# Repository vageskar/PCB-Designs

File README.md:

# PCB-Designs
PCB designs using Cadsoft Eagle

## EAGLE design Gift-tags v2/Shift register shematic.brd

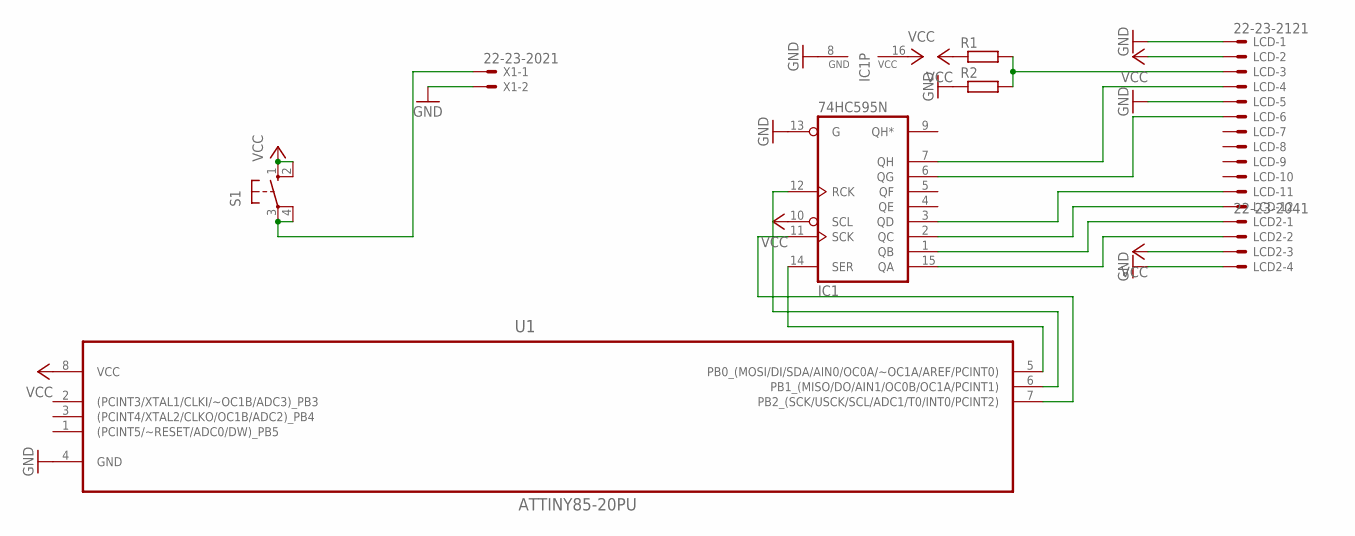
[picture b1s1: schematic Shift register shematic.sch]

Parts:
IC1: 74HC595N; DIL16
LCD: 22-23-2121
LCD2: 22-23-2041
R1, R2: R-EU_0207/10; 0207/10
S1: 40-XX; B3F-40XX
U1: ATTINY85-20PU; DIP254P762X533-8
X1: 22-23-2021

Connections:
GND: IC1.8 (GND), IC1.13 (G), LCD.1, LCD.5, LCD2.4, R2.1, U1.4 (GND), X1.2
unnamed: IC1.15 (QA), LCD2.2
unnamed: IC1.1 (QB), LCD2.1
unnamed: IC1.2 (QC), LCD.12
unnamed: IC1.3 (QD), LCD.11
unnamed: IC1.6 (QG), LCD.6
unnamed: IC1.7 (QH), LCD.4
unnamed: IC1.14 (SER), U1.5 (PB0_(MOSI/DI/SDA/AIN0/OC0A/~OC1A/AREF/P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)
unnamed: IC1.12 (RCK), U1.6 (PB1_(MISO/DO/AIN1/OC0B/OC1A/PCINT1))
unnamed: IC1.11 (SCK), U1.7 (PB2_(SCK/USCK/SCL/ADC1/T0/INT0/PCINT2))
unnamed: LCD.3, R1.2, R2.2
unnamed: S1.3, S1.4 (P1), X1.1
VCC: IC1.10 (SCL), IC1.16 (VCC), LCD.2, LCD2.3, R1.1, S1.1 (S), S1.2 (S1), U1.8 (VCC)

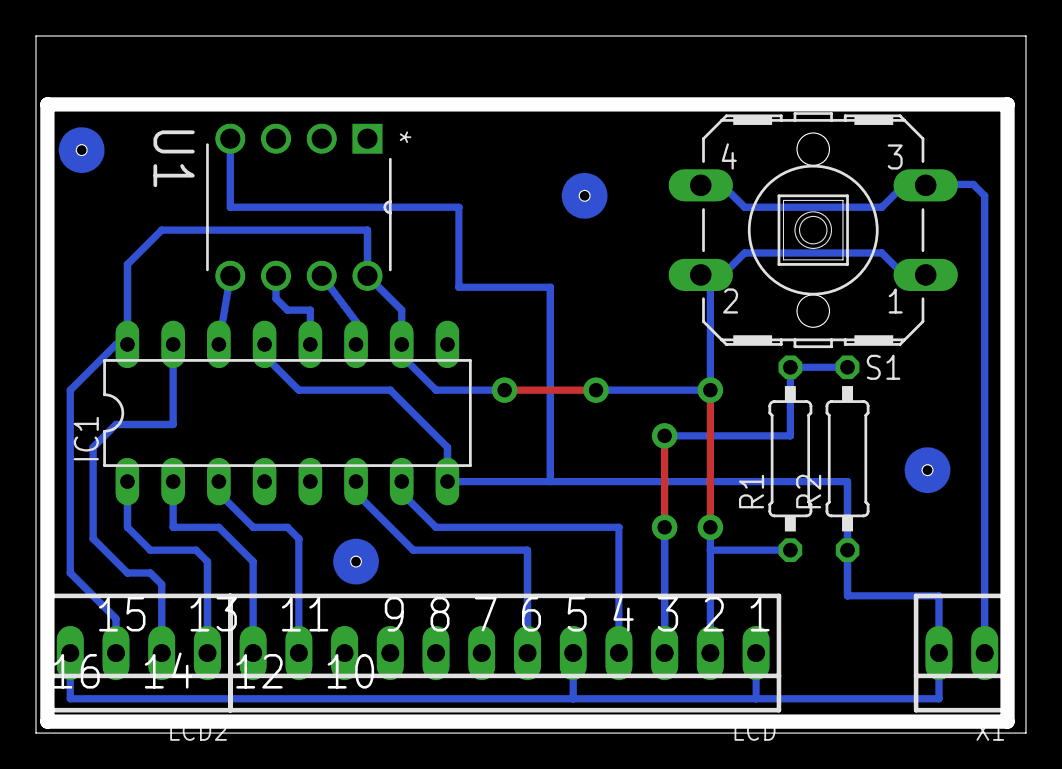
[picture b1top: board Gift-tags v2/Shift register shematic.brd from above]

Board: 2 copper layers, 55.0 x 38.7 mm, 8 parts (0 on the bottom side), 13 nets.

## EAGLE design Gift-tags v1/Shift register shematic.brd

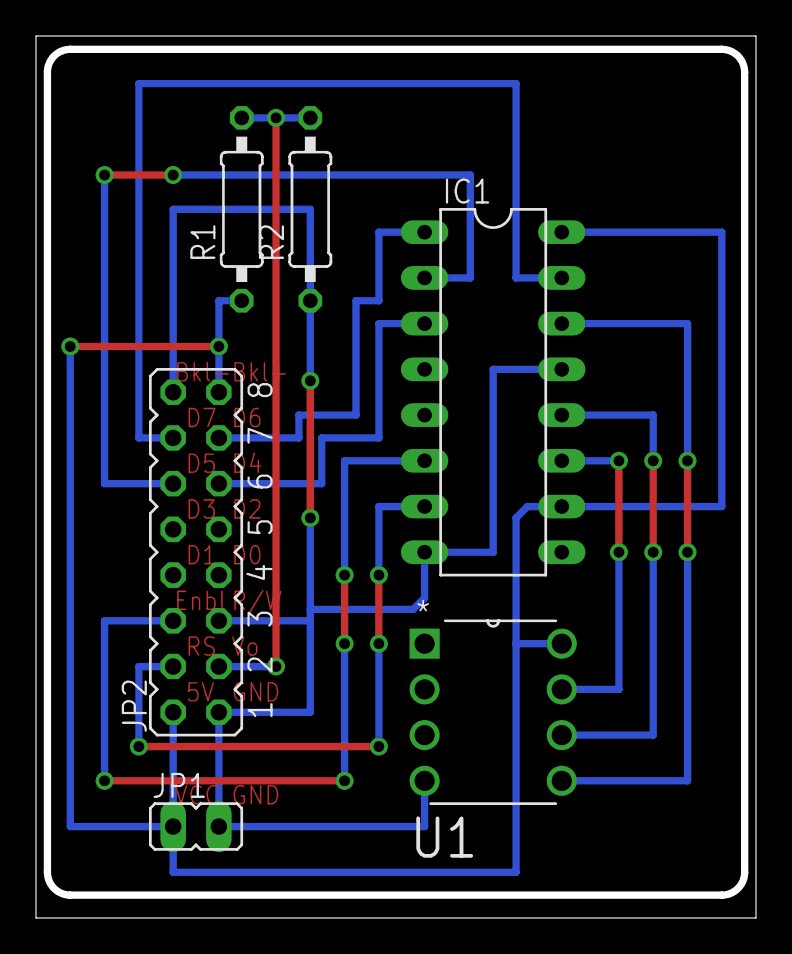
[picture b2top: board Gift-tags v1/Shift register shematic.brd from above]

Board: 2 copper layers, 40.0 x 49.0 mm, 6 parts (0 on the bottom side), 12 nets.

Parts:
IC1: 74HC595N; DIL16
JP1: JP1
JP2: JP8Q
R1, R2: 0207/10
U1: ATTINY85-20PU; DIP254P762X533-8

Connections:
GND: IC1.8, IC1.13, JP1.2, JP2.1, JP2.5, JP2.16, R2.1, U1.4
unnamed: IC1.15, JP2.14
unnamed: IC1.1, JP2.13
unnamed: IC1.2, JP2.12
unnamed: IC1.3, JP2.11
unnamed: IC1.6, JP2.6
unnamed: IC1.7, JP2.4
unnamed: IC1.14, U1.5
unnamed: IC1.12, U1.6
unnamed: IC1.11, U1.7
unnamed: JP2.3, R1.2, R2.2
VCC: IC1.10, IC1.16, JP1.1, JP2.2, JP2.15, R1.1, U1.8

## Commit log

2016-10-10 Adding projects
2016-10-10 Adding project
2016-10-13 Adding files
